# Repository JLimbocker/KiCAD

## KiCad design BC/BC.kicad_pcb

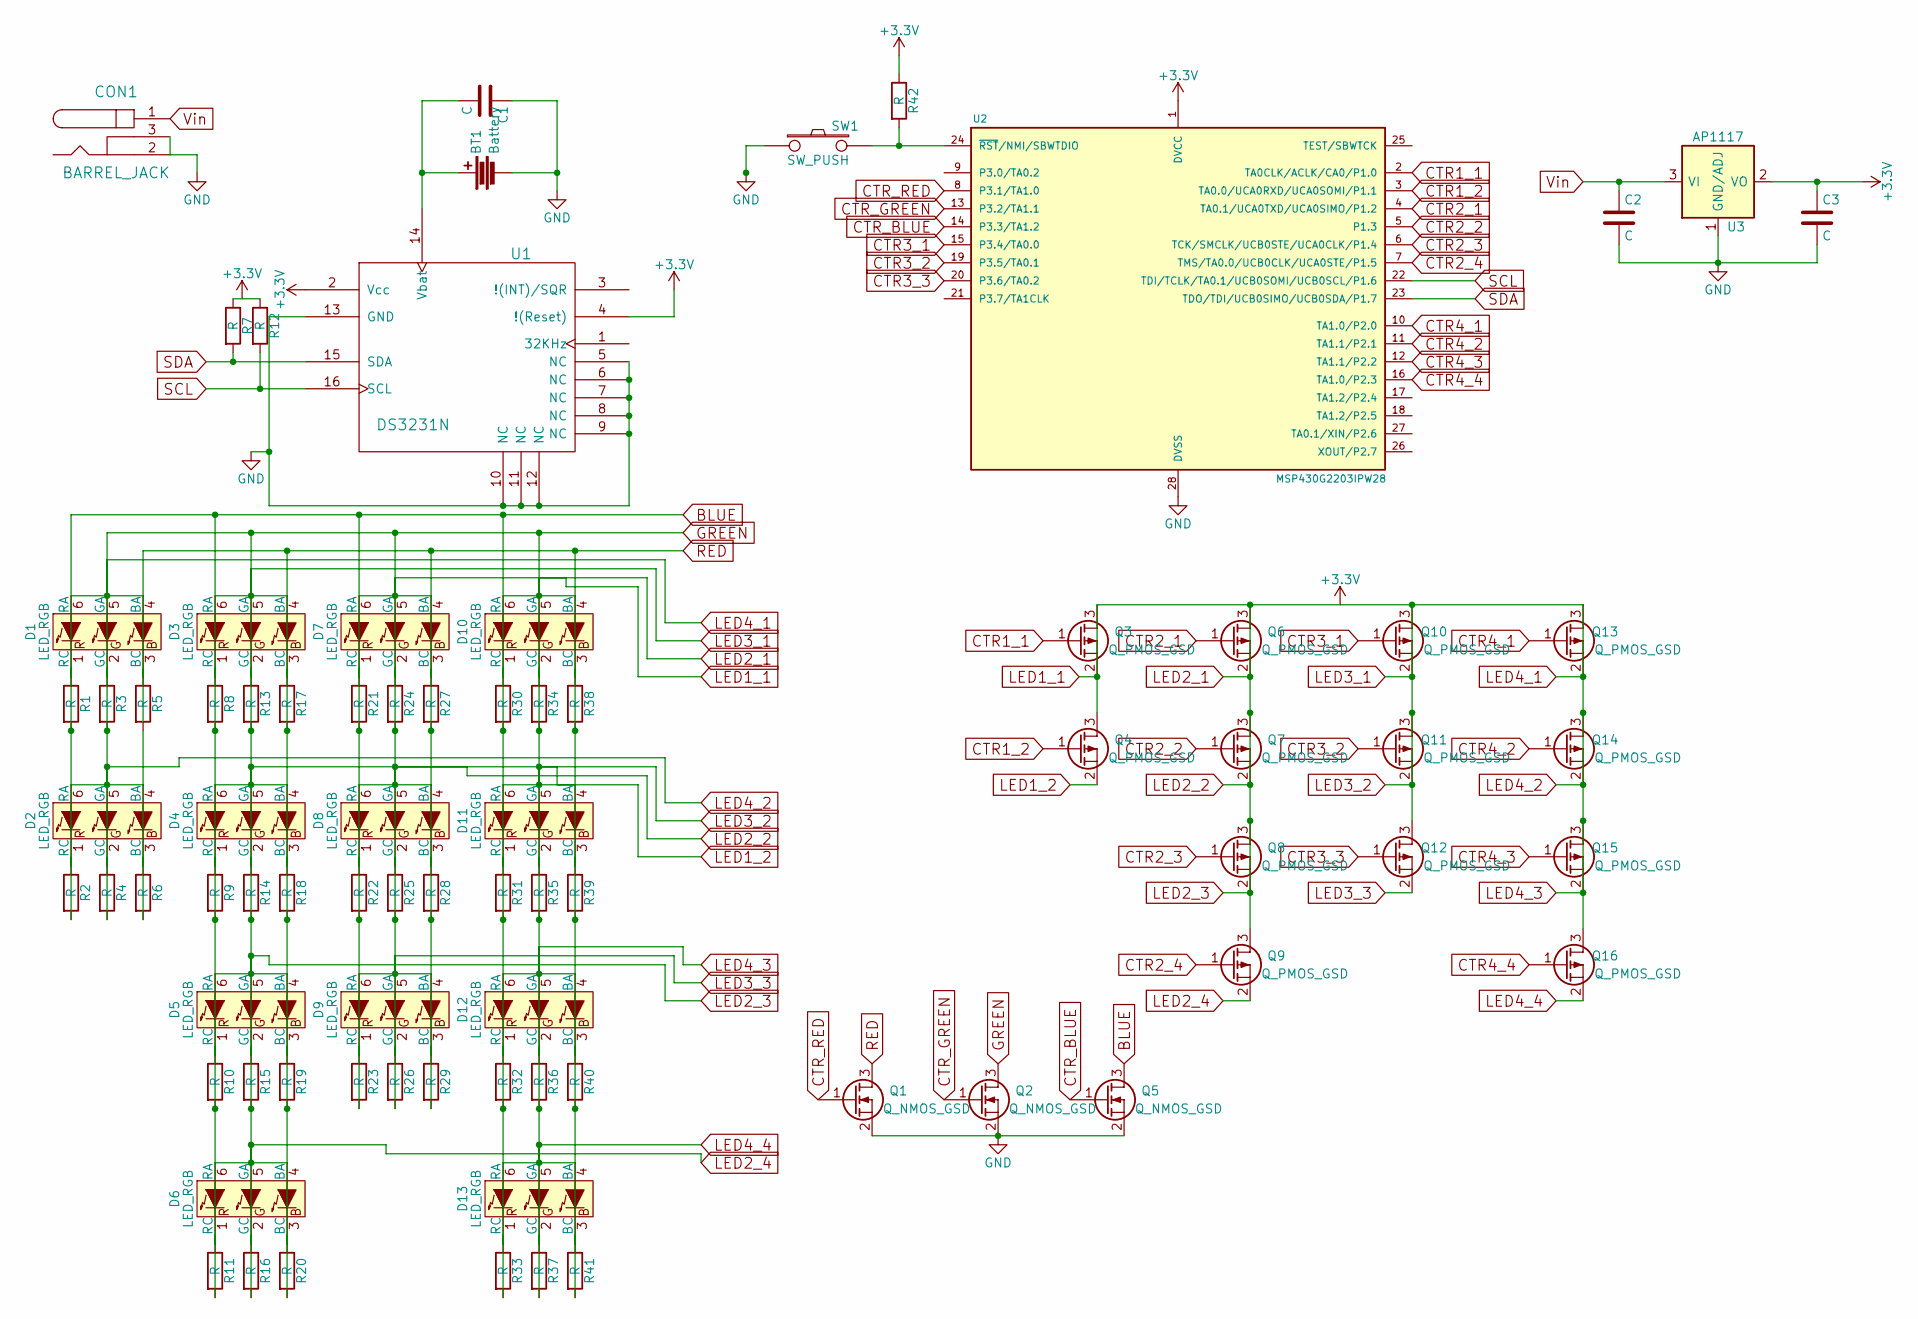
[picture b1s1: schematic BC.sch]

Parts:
BT1: Battery; Banana_Jack_2Pin
C1, C2, C3: C; C_0805_HandSoldering
CON1: BARREL_JACK; Pin_Header_Straight_1x02
D1, D2, D3, D4, D5, D6, D7, D8, D9, D10, D11, D12, D13: LED_RGB; LED_RGB_PLLC-6
Q1, Q2, Q5: Q_NMOS_GSD; SOT-23
Q3, Q4, Q6, Q7, Q8, Q9, Q10, Q11, Q12, Q13, Q14, Q15, Q16: Q_PMOS_GSD; SOT-23
R1, R2, R3, R4, R5, R6, R7, R8, R9, R10, R11, R12, R13, R14, R15, R16, R17, R18, R19, R20, R21, R22, R23, R24, R25, R26, R27, R28, R29, R30, R31, R32, R33, R34, R35, R36, R37, R38, R39, R40, R41, R42: R; R_0805_HandSoldering
SW1: SW_PUSH; SW_SPST_FSMSM
U1: DS3231N; SO-16-L
U2: MSP430G2203IPW28; SOIC-28
U3: AP1117; SOT-23-5

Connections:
BLUE: Q5.3 (D), R1.2, R2.2, R8.2, R9.2, R10.2, R11.2, R21.2, R22.2, R23.2, R30.2, R31.2, R32.2, R33.2
CTR1_1: Q3.1 (G), U2.2 (TA0CLK/ACLK/CA0/P1.0)
CTR1_2: Q4.1 (G), U2.3 (TA0.0/UCA0RXD/UCA0SOMI/P1.1)
CTR2_1: Q6.1 (G), U2.4 (TA0.1/UCA0TXD/UCA0SIMO/P1.2)
CTR2_2: Q7.1 (G), U2.5 (P1.3)
CTR2_3: Q8.1 (G), U2.6 (TCK/SMCLK/UCB0STE/UCA0CLK/P1.4)
CTR2_4: Q9.1 (G), U2.7 (TMS/TA0.0/UCB0CLK/UCA0STE/P1.5)
CTR3_1: Q10.1 (G), U2.15 (P3.4/TA0.0)
CTR3_2: Q11.1 (G), U2.19 (P3.5/TA0.1)
CTR3_3: Q12.1 (G), U2.20 (P3.6/TA0.2)
CTR4_1: Q13.1 (G), U2.10 (TA1.0/P2.0)
CTR4_2: Q14.1 (G), U2.11 (TA1.1/P2.1)
CTR4_3: Q15.1 (G), U2.12 (TA1.1/P2.2)
CTR4_4: Q16.1 (G), U2.16 (TA1.0/P2.3)
CTR_BLUE: Q5.1 (G), U2.14 (P3.3/TA1.2)
CTR_GREEN: Q2.1 (G), U2.13 (P3.2/TA1.1)
CTR_RED: Q1.1 (G), U2.8 (P3.1/TA1.0)
GND: BT1.2, C1.1, C2.2, C3.2, CON1.2, CON1.3, Q1.2 (S), Q2.2 (S), Q5.2 (S), SW1.1, U1.5 (NC), U1.6 (NC), U1.7 (NC), U1.8 (NC), U1.9 (NC), U1.10 (NC), U1.11 (NC), U1.12 (NC), U1.13 (GND), U2.28 (DVSS), U3.1 (GND/ADJ)
unnamed: BT1.1, C1.2, U1.14 (Vbat)
unnamed: D1.1 (RC), R1.1
unnamed: D1.2 (GC), R3.1
unnamed: D1.3 (BC), R5.1
unnamed: D2.1 (RC), R2.1
unnamed: D2.2 (GC), R4.1
unnamed: D2.3 (BC), R6.1
unnamed: D3.1 (RC), R8.1
unnamed: D3.2 (GC), R13.1
unnamed: D3.3 (BC), R17.1
unnamed: D4.1 (RC), R9.1
unnamed: D4.2 (GC), R14.1
unnamed: D4.3 (BC), R18.1
unnamed: D5.1 (RC), R10.1
unnamed: D5.2 (GC), R15.1
unnamed: D5.3 (BC), R19.1
unnamed: D6.1 (RC), R11.1
unnamed: D6.2 (GC), R16.1
unnamed: D6.3 (BC), R20.1
unnamed: D7.1 (RC), R21.1
unnamed: D7.2 (GC), R24.1
unnamed: D7.3 (BC), R27.1
unnamed: D8.1 (RC), R22.1
unnamed: D8.2 (GC), R25.1
unnamed: D8.3 (BC), R28.1
unnamed: D9.1 (RC), R23.1
unnamed: D9.2 (GC), R26.1
unnamed: D9.3 (BC), R29.1
unnamed: D10.1 (RC), R30.1
unnamed: D10.2 (GC), R34.1
unnamed: D10.3 (BC), R38.1
unnamed: D11.1 (RC), R31.1
unnamed: D11.2 (GC), R35.1
unnamed: D11.3 (BC), R39.1
unnamed: D12.1 (RC), R32.1
unnamed: D12.2 (GC), R36.1
unnamed: D12.3 (BC), R40.1
unnamed: D13.1 (RC), R33.1
unnamed: D13.2 (GC), R37.1
unnamed: D13.3 (BC), R41.1
unnamed: R5.2, R6.2
unnamed: R42.2, SW1.2, U2.24 (~RST~/NMI/SBWTDIO)
RED: Q1.3 (D), R17.2, R18.2, R19.2, R20.2, R27.2, R28.2, R29.2, R38.2, R39.2, R40.2, R41.2
SCL: R12.2, U1.16 (SCL), U2.22 (TDI/TCLK/TA0.1/UCB0SOMI/UCB0SCL/P1.6)
SDA: R7.2, U1.15 (SDA), U2.23 (TDO/TDI/UCB0SIMO/UCB0SDA/P1.7)
Vin: C2.1, CON1.1, U3.3 (VI)

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
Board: 2 copper layers, 80 parts (0 on the bottom side), 67 nets, no tracks yet.

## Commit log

2015-12-09 Setting up repo
2015-12-10 Updated for 6pin RGB LED
2015-12-10 Began PCB Layout
2016-01-26 Schematic Update
    Heirarchical Sheets added to schematic
2016-01-26 Finished board schematic
    Completed schematic for test board
2016-02-24 Added DIGDuino
    Removed MdSDE, moved to other repo.
    Added DIGDuino
2016-02-26 Finished Schematic Design
    Schematic Rv1 finished, footprints added
